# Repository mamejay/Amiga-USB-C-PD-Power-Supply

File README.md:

# Amiga USB-C PD Power Supply

A compact power supply that runs a Commodore **Amiga 500 / 600 / 1200** from a USB-C PD charger.
It asks the charger for **15 V** and makes the three Amiga rails on board:

| Rail | Converter | Set point | Rating | Protection |
|---|---|---|---|---|
| +5 V | Silergy SY8205 5 A sync buck → TI TPS259470A eFuse | 5.10 V | **4.5 A continuous** (same as the Commodore A500 PSU; eFuse limit ~5.4 A typ, 4.8 A min) | eFuse cuts the output above **5.64 V** (failed buck can't reach the Amiga), current limit, ~5 ms soft start, SMF5.0A TVS, red fault LED |
| +12 V | TI LMR51430 3 A sync buck | 12.36 V | 1.5 A (Commodore A500 PSU: 1 A; floppy / RS-232 / audio / expansion) | cycle-by-cycle limit + hiccup, SMF13A TVS |
| −12 V | TI LMR51430 as inverting buck-boost (from +12 V) | −12.36 V | 0.5 A+ (Commodore PSU: 0.1 A) | hiccup limit, Schottky clamp against positive excursions, SMF13A TVS |

Input power budget is 45 W (15 V × 3 A), e.g. 5 V 4.5 A + 12 V 1 A + −12 V 0.2 A ≈ 37 W out.
The converters only start once the charger has agreed 15 V (CH224A power-good) **and** VBUS is above ~11.5 V,
so a 5 V-only or non-PD source never powers the Amiga.

## Charger / cable
* USB-C **PD** charger that offers **15 V at 3 A** (any 45 W+ PD charger; 65 W recommended).
* USB-C to USB-C cable rated 3 A or more (normal 60 W cables are fine).

## Board
* **76 × 32 mm** slim board (rev 1.1 / 1.2), 2 layers, 1.6 mm, 1 oz. All SMD parts on the top side (JLCPCB economic PCBA).
* 4 × M3 mounting holes.
* **Cable pads (J2)**, a 2 × 3 block at the right-hand end, 1.4 mm holes (up to 18 AWG). Solder a ready-made Amiga square DIN-5 power cable:

  | Row (top to bottom) | Left pad | Right pad |
  |---|---|---|
  | 1 | +5 V (pad 1, square) | +5 V (pad 2) |
  | 2 | GND (pad 3) | GND (pad 4) |
  | 3 | +12 V (pad 5) | −12 V (pad 6) |

  **Identify every wire of the DIN cable with a multimeter against the Amiga power socket pinout before soldering.**
  Cable wire colours are not standard between suppliers.

* LEDs: green +5 V, green +12 V, green −12 V, red = 5 V eFuse fault.

## Two versions

| | **Rev 1.2** (repo root, recommended) | **Rev 1.1** (`rev1.1/` folder, higher capacity) |
|---|---|---|
| 5 V buck | SY8205, 5 A | TPS56637, 6 A |
| +5 V rating | 4.5 A continuous | **5 A continuous** |
| Parts per board (10 off) | about US$5.37 | about US$7.30 |

Everything else (board size, cable pads, ±12 V) is the same. Rev 1.1 suits heavily expanded machines; see `rev1.1/README.md`.

## Files
* `hw/` – KiCad 10 project (schematic, PCB, project symbol + footprint libraries, DRC/ERC reports).
* `fab/` – JLCPCB order files: Gerbers zip, BOM, CPL and `ORDER NOTES.md`.
* `scripts/` – the generators: `gen_sch.py` (schematic), `place.py` + `build_pcb.py` (placement/board),
  `full.sh` (net classes → Freerouting → pours → GND stitching → DRC loop), `make_fab.py`, `bom_cost.py`.
* `rev1.1/` – complete rev 1.1 (5 A) KiCad project, JLC files and design notes.
* `datasheets/` – not committed (vendor copyright); see the links in `docs/DESIGN.md`.

## Status
Rev 1.2 (cost-down of the slim 76 × 32 mm rev 1.1: SY8205 5 V buck, Fojan 22 µF caps) – routed, ERC 0 / DRC 0
(only 2 cosmetic USB-C silk-at-edge marks), JLC files generated, **not yet built**.
Parts ≈ US$5.37 per board at 10 boards (JLC prices 2026-11-03), 8 extended parts, every part Economic-PCBA eligible.
Rev 1.1 (5 A) is in `rev1.1/` and tagged `v1.1`; rev 1.0 (64 × 46 mm) is tagged `v1.0`. See `docs/DESIGN.md` for the calculations and the bring-up checklist.

## Licence
Copyright © 2026 mamejay. All rights reserved (commercial product). See `LICENSE` and `NOTICE.md`.

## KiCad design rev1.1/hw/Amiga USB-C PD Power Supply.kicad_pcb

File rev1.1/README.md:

# Rev 1.1: higher-capacity 5 V version (TPS56637, 5 A)

This is the same slim 76 × 32 mm board as rev 1.2, with the same cable pads, holes, +12 V and −12 V circuits. Only the 5 V converter is different:

| | Rev 1.1 (this folder) | Rev 1.2 (repo root) |
|---|---|---|
| 5 V buck | TI TPS56637 (6 A, VQFN-HR 3 × 3) | Silergy SY8205 (5 A, SO-8E) |
| L1 | CMLO0650H 3.3 µH | CMLO0650H 4.7 µH |
| eFuse current limit (ILM) | 560 Ω, about 6 A typ, 5.3 A min | 620 Ω, about 5.4 A typ, 4.8 A min |
| +5 V rating | **5 A continuous** | 4.5 A continuous (same as the Commodore A500 PSU) |
| Parts cost | about US$7.30 per board at 10 | about US$5.37 per board at 10 |

Choose rev 1.1 if you run a heavily expanded A500/A600/A1200 (accelerator, RAM, IDE/CF, Gotek and so on) on the 5 V rail.

## Files
* `hw/`: the KiCad 10 project (schematic, PCB, libraries, DRC/ERC reports).
* `fab/`: the JLCPCB files (Gerbers zip, BOM, CPL) and `ORDER NOTES.md`. The CPL already includes the JLC rotation fixes (U1, U4 and U5 at −90, Q1 at +180).
  For Economic PCBA, set the surface finish to HASL or LeadFree HASL, not OSP.
* `docs/`: `DESIGN.md` (rev 1.1 calculations and the bring-up checklist) and the renders.

The generator scripts for this revision are at git tag `v1.1`. The `scripts/` folder at the repo root builds rev 1.2.

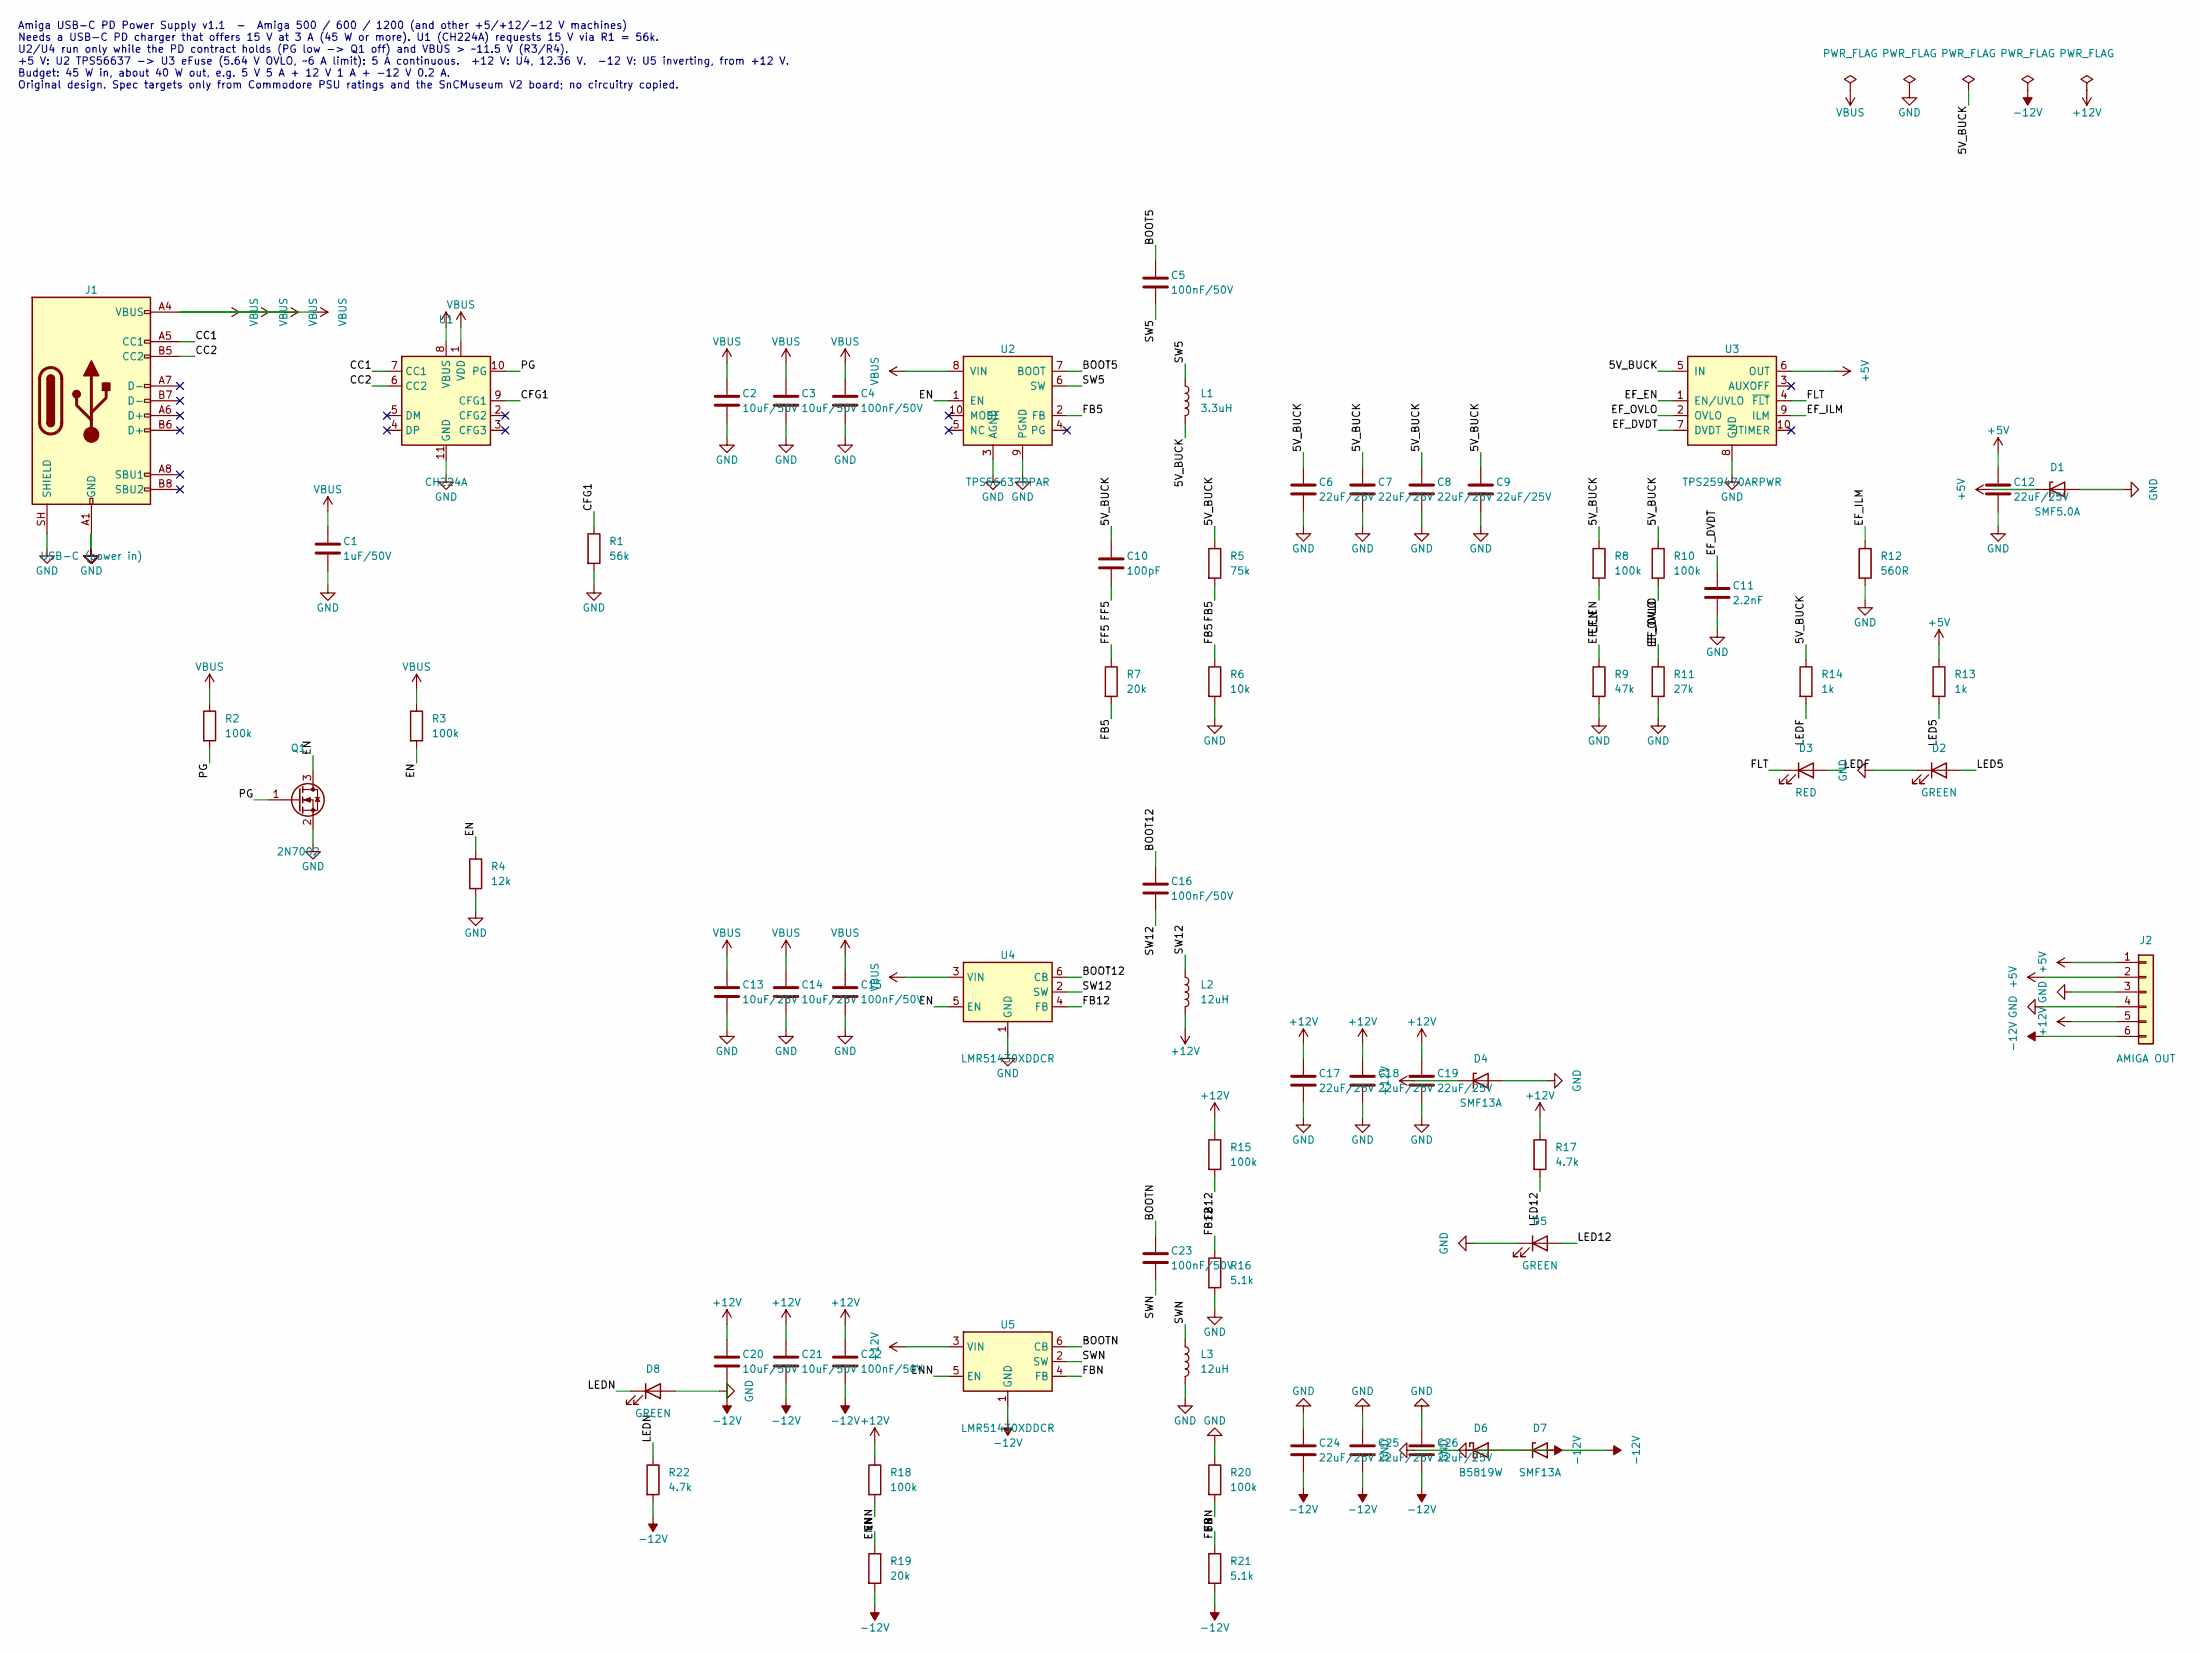
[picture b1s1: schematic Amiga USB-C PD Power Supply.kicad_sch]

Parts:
C1: 1uF/50V; C_0603_1608Metric; LCSC C15849
C2, C3, C20, C21: 10uF/50V; C_1206_3216Metric; LCSC C13585
C4, C5, C15, C16, C22, C23: 100nF/50V; C_0603_1608Metric; LCSC C14663
C6, C7, C8, C9, C12, C17, C18, C19, C24, C25, C26: 22uF/25V; C_0805_2012Metric; LCSC C7419435
C10: 100pF; C_0603_1608Metric; LCSC C14858
C11: 2.2nF; C_0603_1608Metric; LCSC C1604
C13, C14: 10uF/25V; C_0805_2012Metric; LCSC C15850
D1: SMF5.0A; D_SOD-123F; LCSC C19077497
D2, D5, D8: GREEN; LED_0805_2012Metric; LCSC C2297
D3: RED; LED_0805_2012Metric; LCSC C84256
D4, D7: SMF13A; D_SOD-123F; LCSC C41376087
D6: B5819W; D_SOD-123; LCSC C8598
J1: USB-C (power in); USB_C_Receptacle_HRO_TYPE-C-31-M-12; LCSC C165948
J2: AMIGA OUT; WirePads_2x03_P3.81mm_D1.4mm
L1: 3.3uH; L_Chilisin_CMLO0650H; LCSC C439008
L2, L3: 12uH; L_FH_FNR6045; LCSC C168077
Q1: 2N7002; SOT-23; LCSC C8545
R1: 56k; R_0603_1608Metric; LCSC C23206
R2, R3, R8, R10, R15, R18, R20: 100k; R_0603_1608Metric; LCSC C25803
R4: 12k; R_0603_1608Metric; LCSC C22790
R5: 75k; R_0603_1608Metric; LCSC C23242
R6: 10k; R_0603_1608Metric; LCSC C25804
R7, R19: 20k; R_0603_1608Metric; LCSC C4184
R9: 47k; R_0603_1608Metric; LCSC C25819
R11: 27k; R_0603_1608Metric; LCSC C22967
R12: 560R; R_0603_1608Metric; LCSC C23204
R13, R14: 1k; R_0603_1608Metric; LCSC C21190
R16, R21: 5.1k; R_0603_1608Metric; LCSC C23186
R17, R22: 4.7k; R_0603_1608Metric; LCSC C23162
U1: CH224A; SSOP-10-1EP_3.9x4.9mm_P1mm_EP2.1x3.3mm; LCSC C42459160
U2: TPS56637RPAR; TI_RPA0010A_VQFN-HR-10_3x3mm; LCSC C841386
U3: TPS259470ARPWR; TI_RPW0010A_VQFN-10-HR_2x2mm; LCSC C3662799
U4, U5: LMR51430XDDCR; TSOT-23-6; LCSC C5185863

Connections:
+5V: C12.1, D1.1 (K), J2.1, J2.2, R13.1, U3.6 (OUT)
+12V: C17.1, C18.1, C19.1, C20.1, C21.1, C22.1, D4.1 (K), J2.5, L2.2, R15.1, R17.1, R18.1, U5.3 (VIN)
-12V: C20.2, C21.2, C22.2, C24.2, C25.2, C26.2, D6.2 (A), D7.2 (A), J2.6, R19.2, R21.2, R22.2, U5.1 (GND)
/5V_BUCK: C6.1, C7.1, C8.1, C9.1, C10.1, L1.2, R5.1, R8.1, R10.1, R14.1, U3.5 (IN)
/BOOT5: C5.1, U2.7 (BOOT)
/BOOT12: C16.1, U4.6 (CB)
/BOOTN: C23.1, U5.6 (CB)
/CC1: J1.A5 (CC1), U1.7 (CC1)
/CC2: J1.B5 (CC2), U1.6 (CC2)
/CFG1: R1.1, U1.9 (CFG1)
/EF_DVDT: C11.1, U3.7 (DVDT)
/EF_EN: R8.2, R9.1, U3.1 (EN/UVLO)
/EF_ILM: R12.1, U3.9 (ILM)
/EF_OVLO: R10.2, R11.1, U3.2 (OVLO)
/EN: Q1.3 (D), R3.2, R4.1, U2.1 (EN), U4.5 (EN)
/ENN: R18.2, R19.1, U5.5 (EN)
/FB5: R5.2, R6.1, R7.2, U2.2 (FB)
/FB12: R15.2, R16.1, U4.4 (FB)
/FBN: R20.2, R21.1, U5.4 (FB)
/FF5: C10.2, R7.1
/FLT: D3.1 (K), U3.4 (~FLT)
/LED5: D2.2 (A), R13.2
/LED12: D5.2 (A), R17.2
/LEDF: D3.2 (A), R14.2
/LEDN: D8.1 (K), R22.1
/PG: Q1.1 (G), R2.2, U1.10 (PG)
/SW5: C5.2, L1.1, U2.6 (SW)
/SW12: C16.2, L2.1, U4.2 (SW)
/SWN: C23.2, L3.1, U5.2 (SW)
GND: C1.2, C2.2, C3.2, C4.2, C6.2, C7.2, C8.2, C9.2, C11.2, C12.2, C13.2, C14.2, C15.2, C17.2, C18.2, C19.2, C24.1, C25.1, C26.1, D1.2 (A), D2.1 (K), D4.2 (A), D5.1 (K), D6.1 (K), D7.1 (K), D8.2 (A), J1.A1 (GND), J1.A12 (GND), J1.B1 (GND), J1.B12 (GND), J1.SH (SHIELD), J2.3, J2.4, L3.2, Q1.2 (S), R1.2, R4.2, R6.2, R9.2, R11.2, R12.2, R16.2, R20.1, U1.11 (GND), U2.3 (AGND), U2.9 (PGND), U3.8 (GND), U4.1 (GND)
VBUS: C1.1, C2.1, C3.1, C4.1, C13.1, C14.1, C15.1, J1.A4 (VBUS), J1.A9 (VBUS), J1.B4 (VBUS), J1.B9 (VBUS), R2.1, R3.1, U1.1 (VDD), U1.8 (VBUS), U2.8 (VIN), U4.3 (VIN)

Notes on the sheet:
Amiga USB-C PD Power Supply v1.1 - Amiga 500 / 600 / 1200 (and other +5/+12/-12 V machines) Needs a USB-C PD charger that offers 15 V at 3 A (45 W or more). U1 (CH224A) requests 15 V via R1 = 56k. U2/U4 run only while the PD contract holds (PG low -> Q1 off) and VBUS > ~11.5 V (R3/R4). +5 V: U2 TPS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

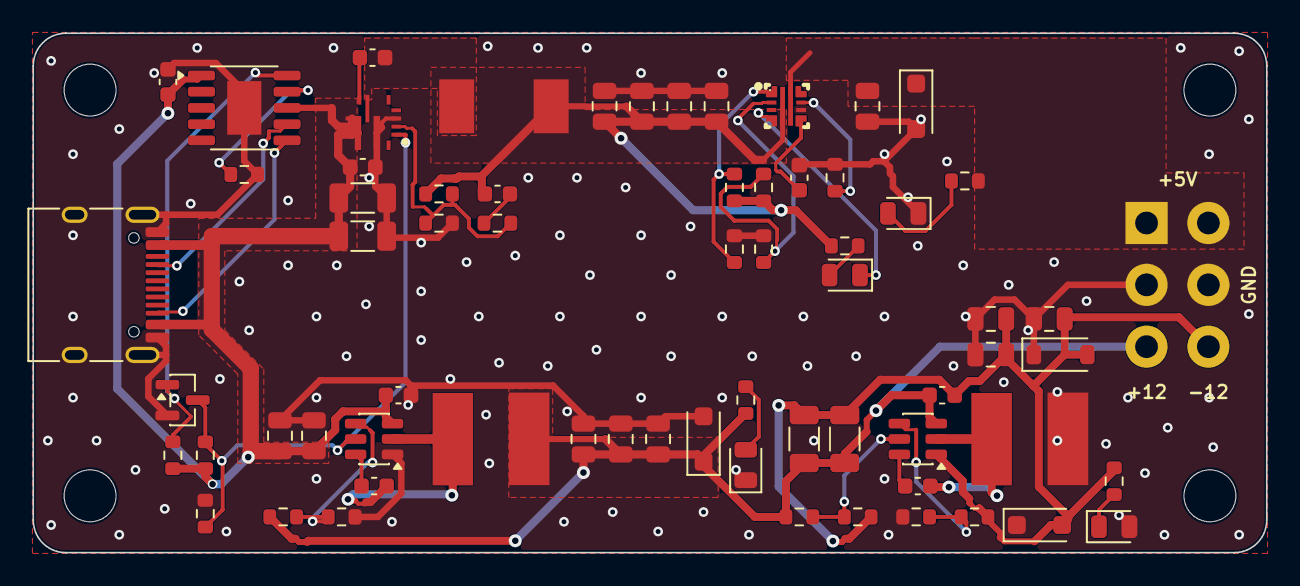
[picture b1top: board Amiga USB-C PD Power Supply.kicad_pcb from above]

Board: 2 copper layers, 76.0 x 32.0 mm, 71 parts (0 on the bottom side), 31 nets.

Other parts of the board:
H1, H2, H3, H4: M3; MountingHole_3.2mm_M3

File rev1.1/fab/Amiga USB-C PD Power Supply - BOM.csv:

Comment,Designator,Footprint,LCSC Part #
1uF/50V,C1,0603,C15849
10uF/50V,"C2,C3,C20,C21",1206,C13585
100nF/50V,"C4,C5,C15,C16,C22,C23",0603,C14663
22uF/25V,"C6,C7,C8,C9,C12,C17,C18,C19,C24,C25,C26",0805,C7419435
100pF,C10,0603,C14858
2.2nF,C11,0603,C1604
10uF/25V,"C13,C14",0805,C15850
SMF5.0A,D1,SOD-123F,C19077497
GREEN,"D2,D5,D8",0805,C2297
RED,D3,0805,C84256
SMF13A,"D4,D7",SOD-123F,C41376087
B5819W,D6,SOD-123,C8598
USB-C (power in),J1,TYPE-C-31-M-12,C165948
3.3uH,L1,CMLO0650H,C439008
12uH,"L2,L3",L_FH_FNR6045,C168077
2N7002,Q1,SOT-23,C8545
56k,R1,0603,C23206
100k,"R2,R3,R8,R10,R15,R18,R20",0603,C25803
12k,R4,0603,C22790
75k,R5,0603,C23242
10k,R6,0603,C25804
20k,"R7,R19",0603,C4184
47k,R9,0603,C25819
27k,R11,0603,C22967
560R,R12,0603,C23204
1k,"R13,R14",0603,C21190
5.1k,"R16,R21",0603,C23186
4.7k,"R17,R22",0603,C23162
CH224A,U1,SSOP-10,C42459160
TPS56637RPAR,U2,VQFN-HR-10_3x3,C841386
TPS259470ARPWR,U3,VQFN-10-HR_2x2,C3662799
LMR51430XDDCR,"U4,U5",TSOT-23-6,C5185863
